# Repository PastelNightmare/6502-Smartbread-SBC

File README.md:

# Archiving, for now! I don't recommend using V1 of the board as of now.
As I play around with the finished PCB, I realized there are a few issues with it. 
- A13 is not connected to the RAM chip, so you have to make a jumper to it from elsewhere. 
- The below mentioned difference in clock generation from other processors to the WDC version.
- I'm using the WDC 65C22S, which does NOT have an open-drain interrupt output! It has a totem pole ouput! Right now, it's currently wired as if it were open drain, which is fine as long as you **don't use interrupts.** If you do though, you will short circuit the IRQ lines of the VIA.

# Upcoming hardware changes? 
- Reconnect A13, obviously.
- Make the system clock with WDC parts in mind
- Add schottky diodes on the VIA interrupts to connect them with the other open drain interrupts. Fine at 2mhz clock speed.
- Change address decoding to use Daryl Rictors DEC-1. https://sbc.rictor.org/decoder.html

# Upcoming software changes? 
- A customized version of EHBasic, which I've already made. Includes commands for sound, clearing screen, and returning to the monitor.
- Updating VGM player to load VGM out of RAM instead of ROM, and commented to explain better what it is doing. 
- Porting WozMon to this board for easier data entry. DeMon is fine, but it was more a project for me anyway. 
- A better terminal emulator program
- Eventually, using the new interrupts to allow streaming of VGM from the serial port. But that is a long time off. 

# IMPORTANT DESIGN NOTE
Due to a design difference with the WDC version of the 65C02 processor, this board will not work with WDC chips without a small modification. See "Using a WDC 65C02" below.

# SmartBread: A 6502 based single-board computer 
Its name came from a friend who called it this when they saw my initial prototypes on a breadboard. MintSpark Electronics was the working "maker name" for my projects, though it may not be for long. Other than another 6502 based single board computer, of which many exist, this was many firsts for me. Starting in 2017, I had a goal to build a 6502 system on a breadboard. As it grew, it became my first real endeavour into 6502 assembly, coding for an actual system, trying to make user friendly software, and PCB making. I now have working PCBs, a few programs, and much more work to do. 

Repo includes software, PCB gerber files and resources. ROM included has DeMon 4.0 and EhBASIC w/ its cold start monitor. Other files can be added and recompiled as desired 

Software assumes you are using the Kowalski 6502 simulator for assmebly. https://sbc.rictor.org/kowalski.html 

# Disclaimer: 
This was my first stab at assembly of any kind. While the code does exactly what I want it to do for this system, I understand that my code is not pretty by any stretch, and there is tons of room for improvement. I'm a novice, so please go easy on me. Some things like address decoding were figured out with the help of the 6502 forum and the 6502 Primer by Garth Wilson. Found at: http://wilsonminesco.com/

# Specs
- 65C02 processor running at 2mhz
- 2x 65C22 VIA (versatile interface adapter) chips
- 1x 65C51 ACIA (UART) chip
- SN76489 soundchip
- 32KB EEPROM (AT28C256)
- 16KB RAM (Alliance AS6C62256. 32kb chip, address decoding makes it 16kb)
- ATTINY26 for keyboard input
- Quad NAND gate 74 chip for address decoding
- Jumpers to fully configure serial port settings
- GPIO port, spare 8 bit parallel. 5v and GND also available. 
- PS2 keyboard input
- RCA output for sound. 
- Displays to charcter LCD or serial using any terminal device (board has a slot for the BatSocks tellymate tiny for this purpose http://www.batsocks.co.uk/products/Other/TellyMate%20Tiny.htm)

# Parts list
- R1-R6: 3.3k through hole resistor
- R7, R8: 10k through hole resistor
- R9: 370 ohm resistor. 
- C1: 1uf electrolytic capacitor. 
- All other capacitors: 100nf filter. Ceramic disc.
- 6502CLCK: ECS-100AX-018 oscillator, 2MHz
- SNCLCK: ECS-100AX-018 oscillator, 4MHz
- SERCLCK: ECS-100AX-018 oscillator, 1.8432MHz
- 65C02 processor
- VIA1, VIA2: 65C22 VIA chips (keyboard doesn't work right with non-CMOS versions)
- ACIA: 65C51 ACIA chip
- ROM: AT28C256
- RAM: Alliance AS6C62256
- ADDR: CD74HCT132E
- SN: Texas Instruments: SN76489
- ATTINY26: Atmel ATTINY26
- POWER: 5v through header, or surface mount USB Mini B jack. 

# Included Software
## DeMon 4.0
DeMon (DEvice MONitor) 4.0 is a basic memory monitor for the system. You can read the memory map, write to the memory map, run code, send commands directly to the sound chip, and much more. 
### Commands
All commands are processed by pressing enter. Accepts input from onboard PS2 keyboard or ACIA (with FTDI breakout)

| Command | Example | Description |         
| --------------- | --------------- | --------------- |
| Read  | 4000  | Displays data at address 0x4000  |
| List |L 2000.20FF| Will display all data between addresses 0x2000 and 0x20FF |
| Write  | W 2000 FF | Writes 0xFF at address 0x2000  |
| Write next | 00 | Data byte preceded with a space will write data to next location. MUST USE WRITE COMMAND FIRST |
| Run | R 2000 | Runs code starting at address 2000 | 
| Clear | CL | Clears all displays |
| Sound | S FF | Sends 0xFF to sound chip and makes the chip process it | 

## VGM player
A simple VGM player to play VGM files for the SN76489 sound chip. Expects raw VGM hex at 8900 (0900 if you're burning to ROM). Could easily be changed to load hex out of RAM instead with one line of code. 

## Enhanced 6502 BASIC 2.22 (EhBASIC) port
Made by Lee Davison, information: http://retro.hansotten.nl/6502-sbc/lee-davison-web-site/enhanced-6502-basic/. Ported to SmartBread by me. **COMPILING NOTE:** in order to compile EhBASIC, point the include line at the beginning of the Minimal Monitor to where you've downloaded EHBASIC.ASM. Minimal monitor starts at A000 and should be used to cold start BASIC! 

# Port Description
- GPIO - 8 bit parallel GPIO port. Can attach LCD to this port to work natively with DeMon, but it isn't required and can be used for whatever else the end user desires. The current board DOES NOT have the LCD enable line on this port, but it will be added to a future revision. 
- TM - Tellymate Tiny can be connected here for composite display. The part is discontinued, but eagle files and firmware exist on the Batsocks website. 
- Serial - Gives control lines for the ACIA ports, along with GNDs next to each one. Allows these status lines to be jumpered to ground, which **should** be done for most operations. (DTR, RTS, CTS, DCD) Also provides 5v and GND for user. Can connect to a TTL to RS232 converter for any type of serial display. 
- CLKMODE - Shorting these two pins with solder or a jumper allows the serial clock to also run the processor clock. This saves one part, but makes the CPU run slightly slower. 

# Using a WDC 65C02
In order to use a WDC version of the processor in the current revision, there is a slight modification to the board that must be made. Pin 39 (PHI2O) on the chip must be lifted out of the socket or removed. Then on the underside of the board, you must bridge a connection between Pin 39 and Pin 37 of the CPU socket. 

Traditionally, you provide the clock frequency to the CPU via PHI0/PHI2 input, then drive the rest of peripherals from PHI2O output from the CPU. The board was made with this in mind. WDC chips, however, do not test or guarantee the usability of the PHI2O output. They recommend that everything onboard receives its clock from the main oscillator driving the CPU. By bridging these two points on the board and lifting pin 39 from the chip, you are routing the clock in this manner. Future board revisions will have this as a jumper to ensure compatiblity. 

# To-do list / Wishlist 
- Update display to a new, non-discontinued solution. For now, Tellymate Tiny could be used, or provided serial pins can be attached to any device with a TTL to RS232 converter (Max232 and the like): Breakout USB boards, Converted RS232 port to a real glass terminal, etc. 
- Improve code by removing useless structures / subroutines
- Adding a binary load command to DeMon load binary data directly into memory from serial port. 
- Either standalone or built-in assembly evnironment for DeMon. 
- Text editor prorgram
- SPI protocol for various peripherals. 
- Cassette interface. 
- Rewrite my old code. The VGM player is old and hard to read. This was before I knew much about anything coding wise. 
- Write a terminal emulator program. I did make SimTerm originally, but it is hot garbage.

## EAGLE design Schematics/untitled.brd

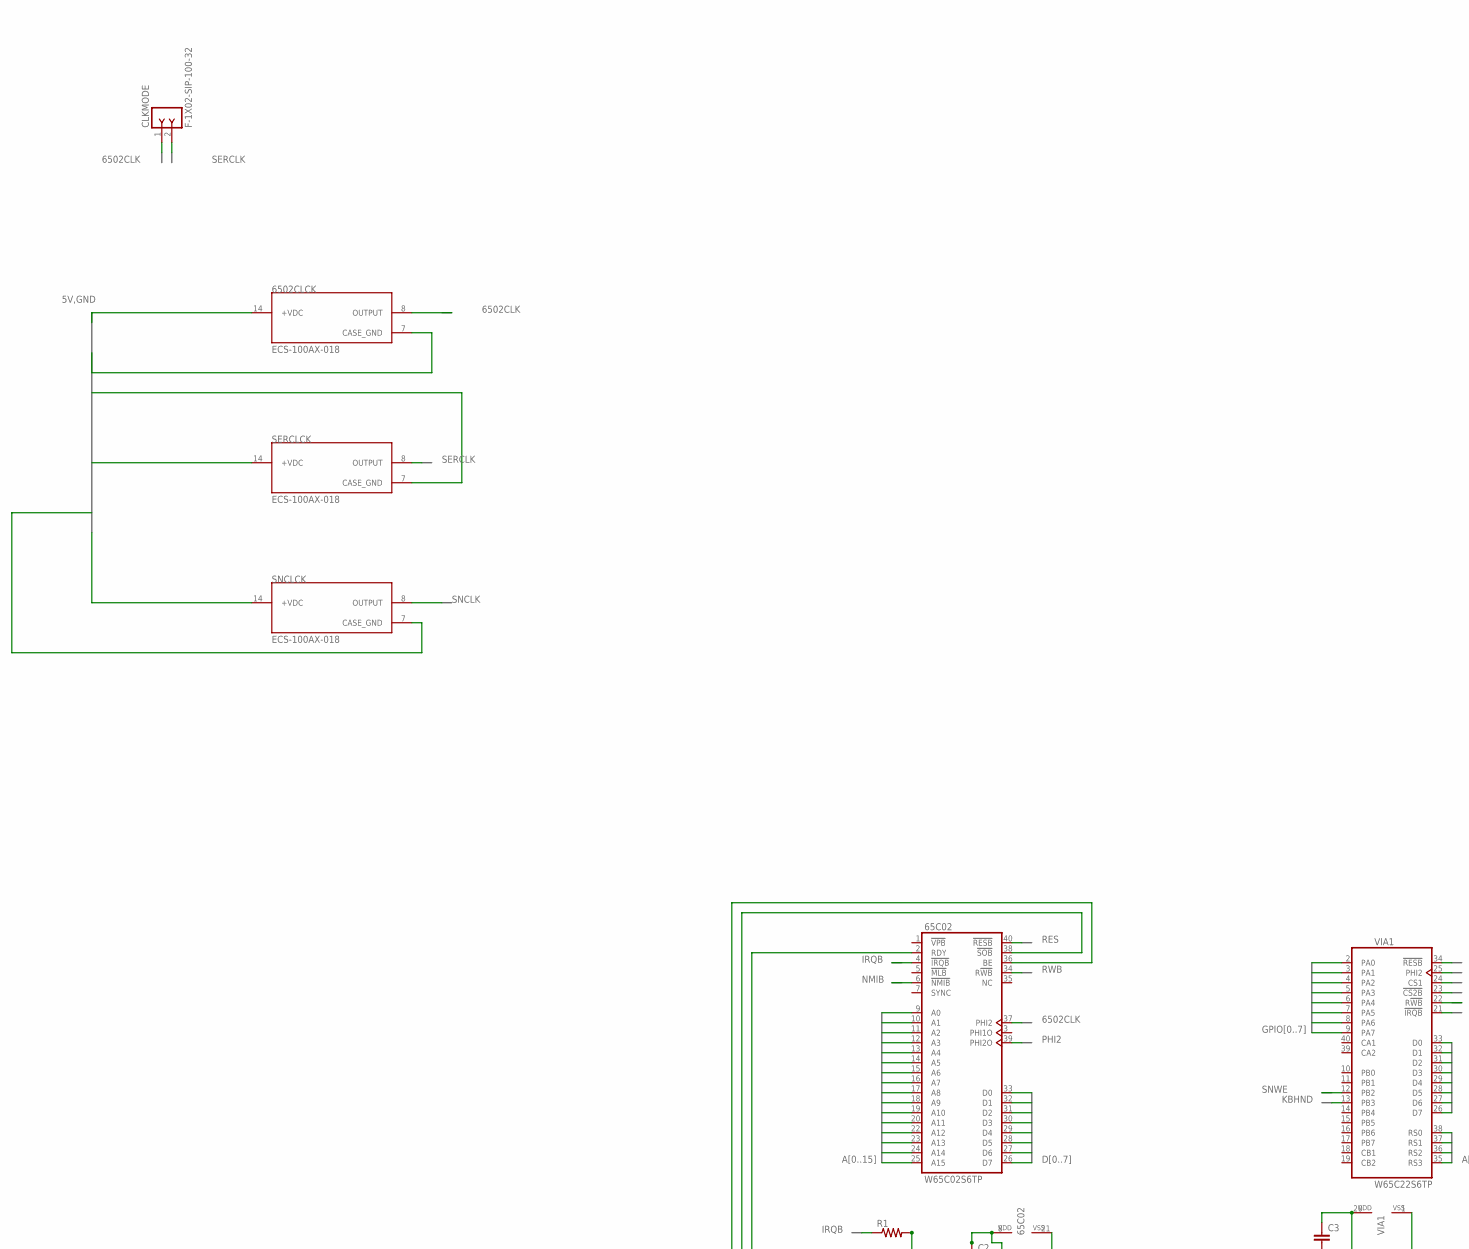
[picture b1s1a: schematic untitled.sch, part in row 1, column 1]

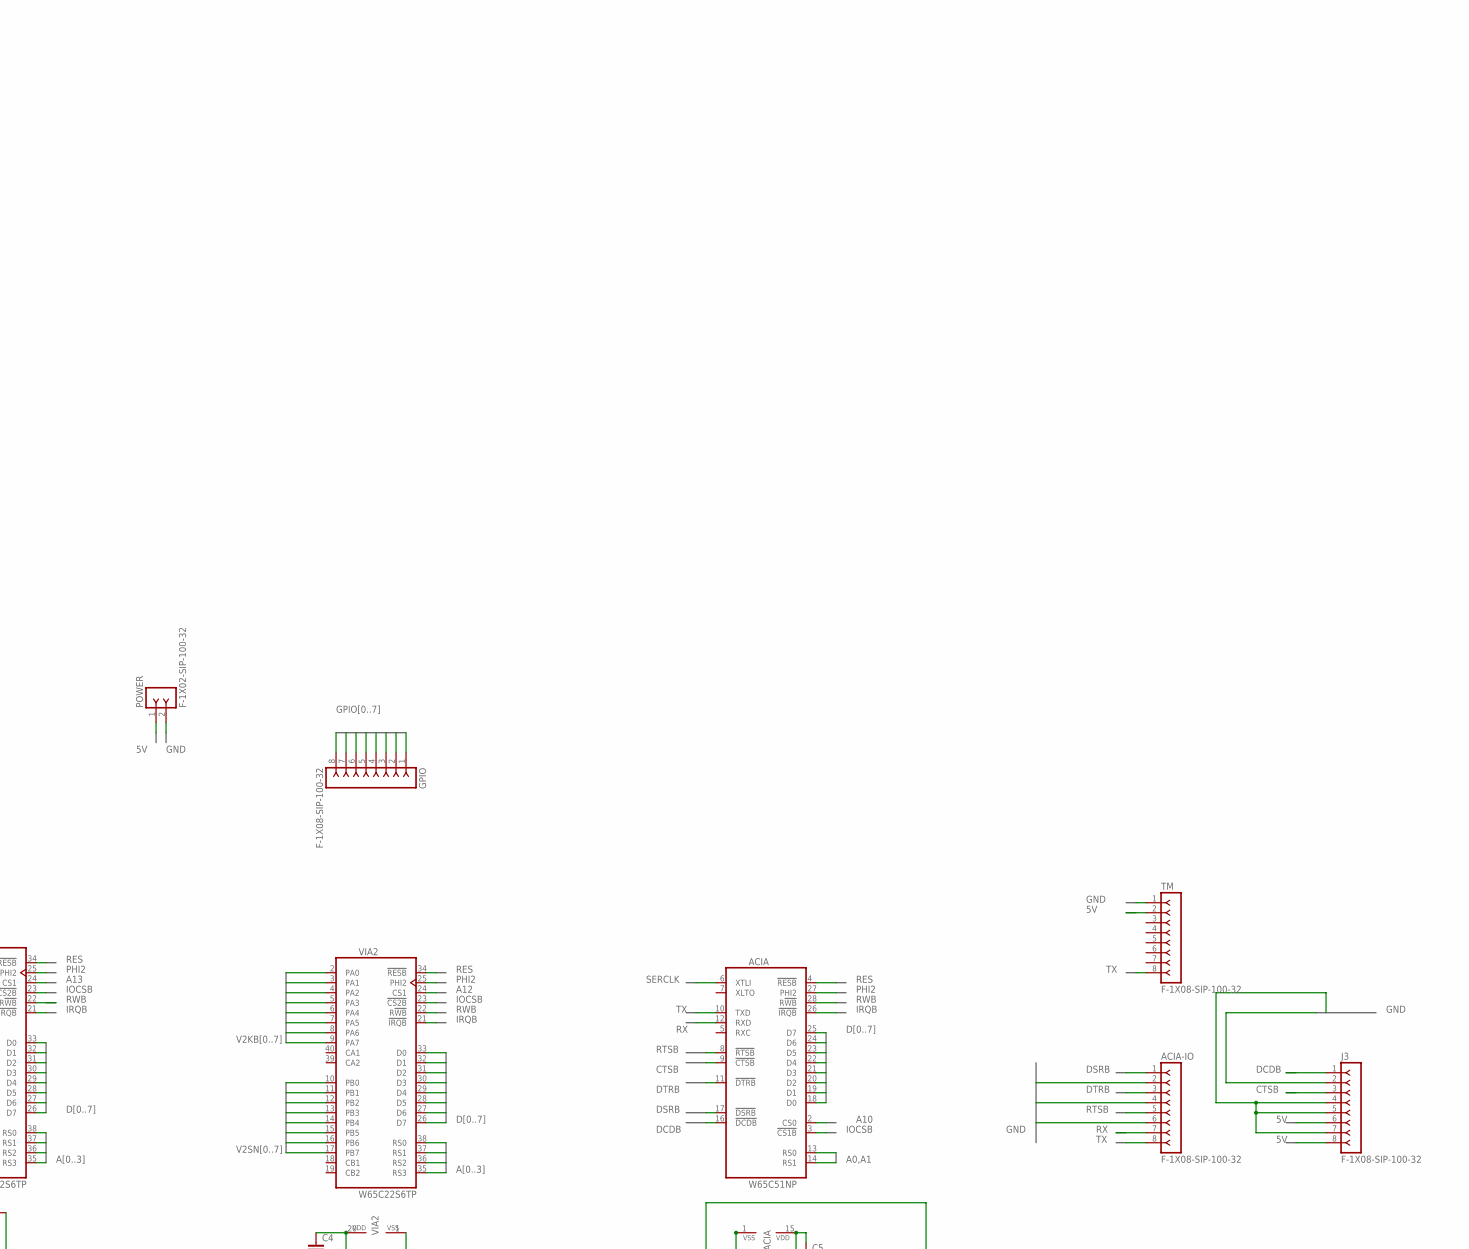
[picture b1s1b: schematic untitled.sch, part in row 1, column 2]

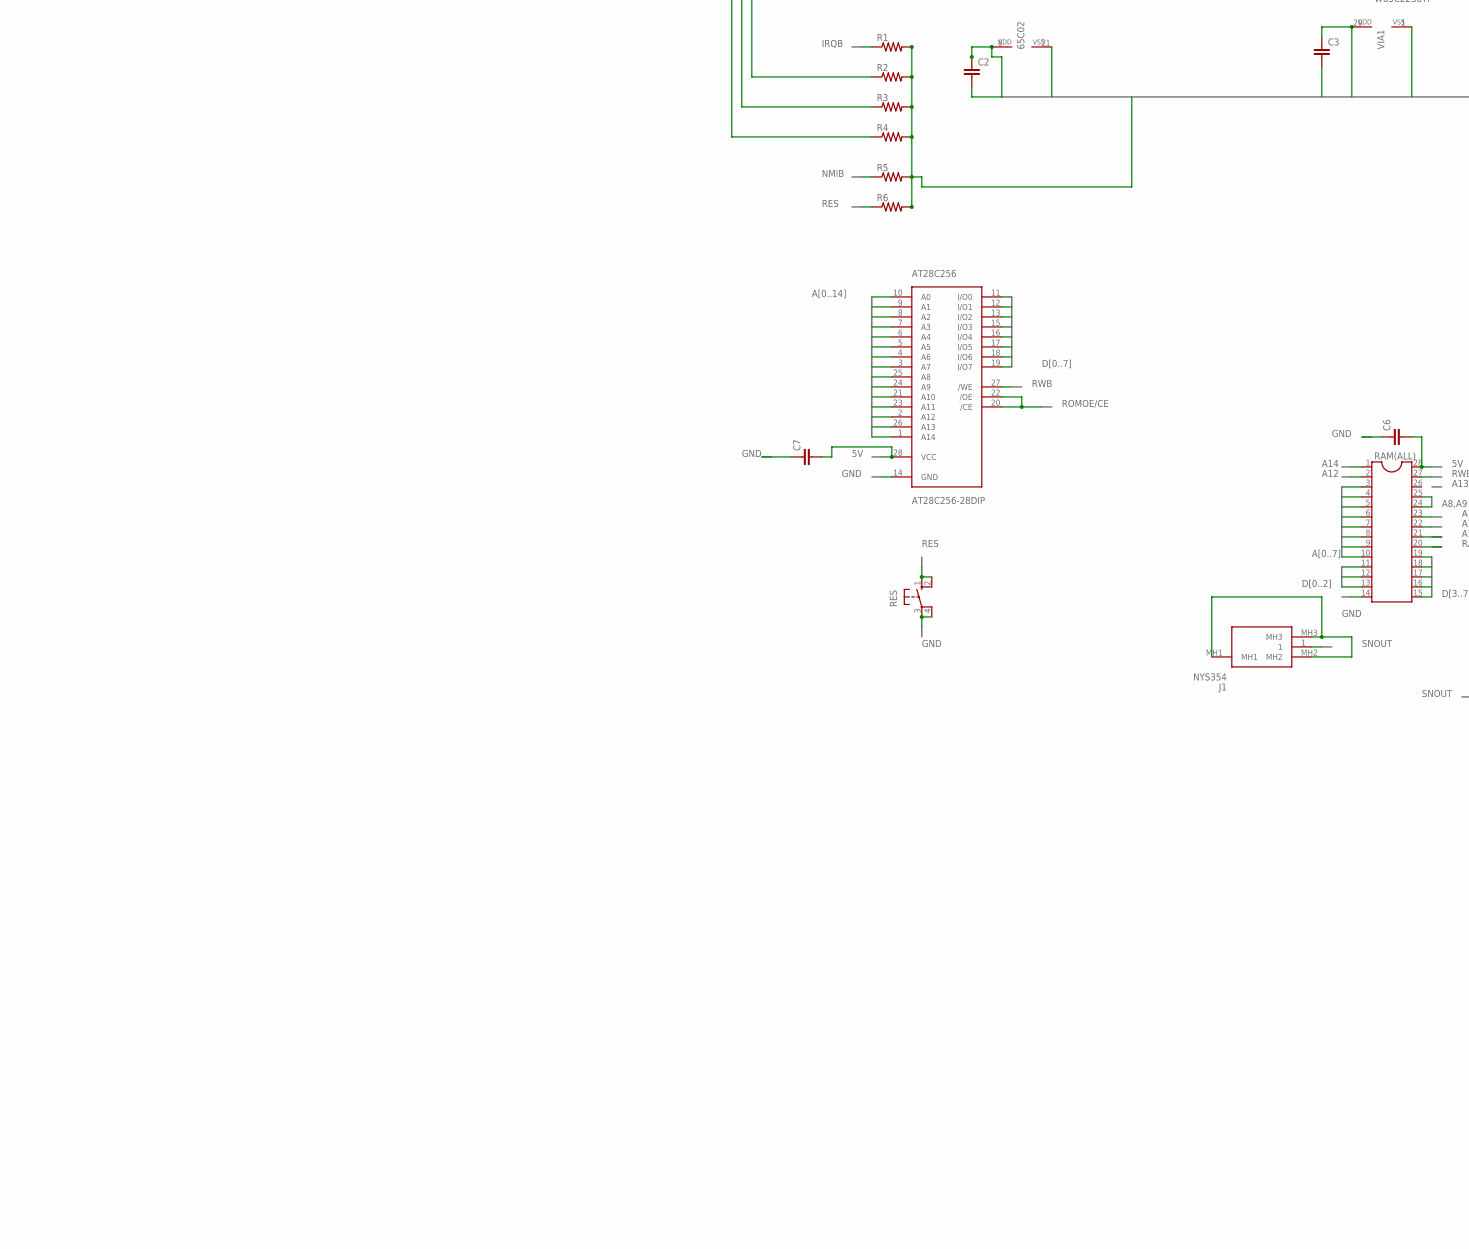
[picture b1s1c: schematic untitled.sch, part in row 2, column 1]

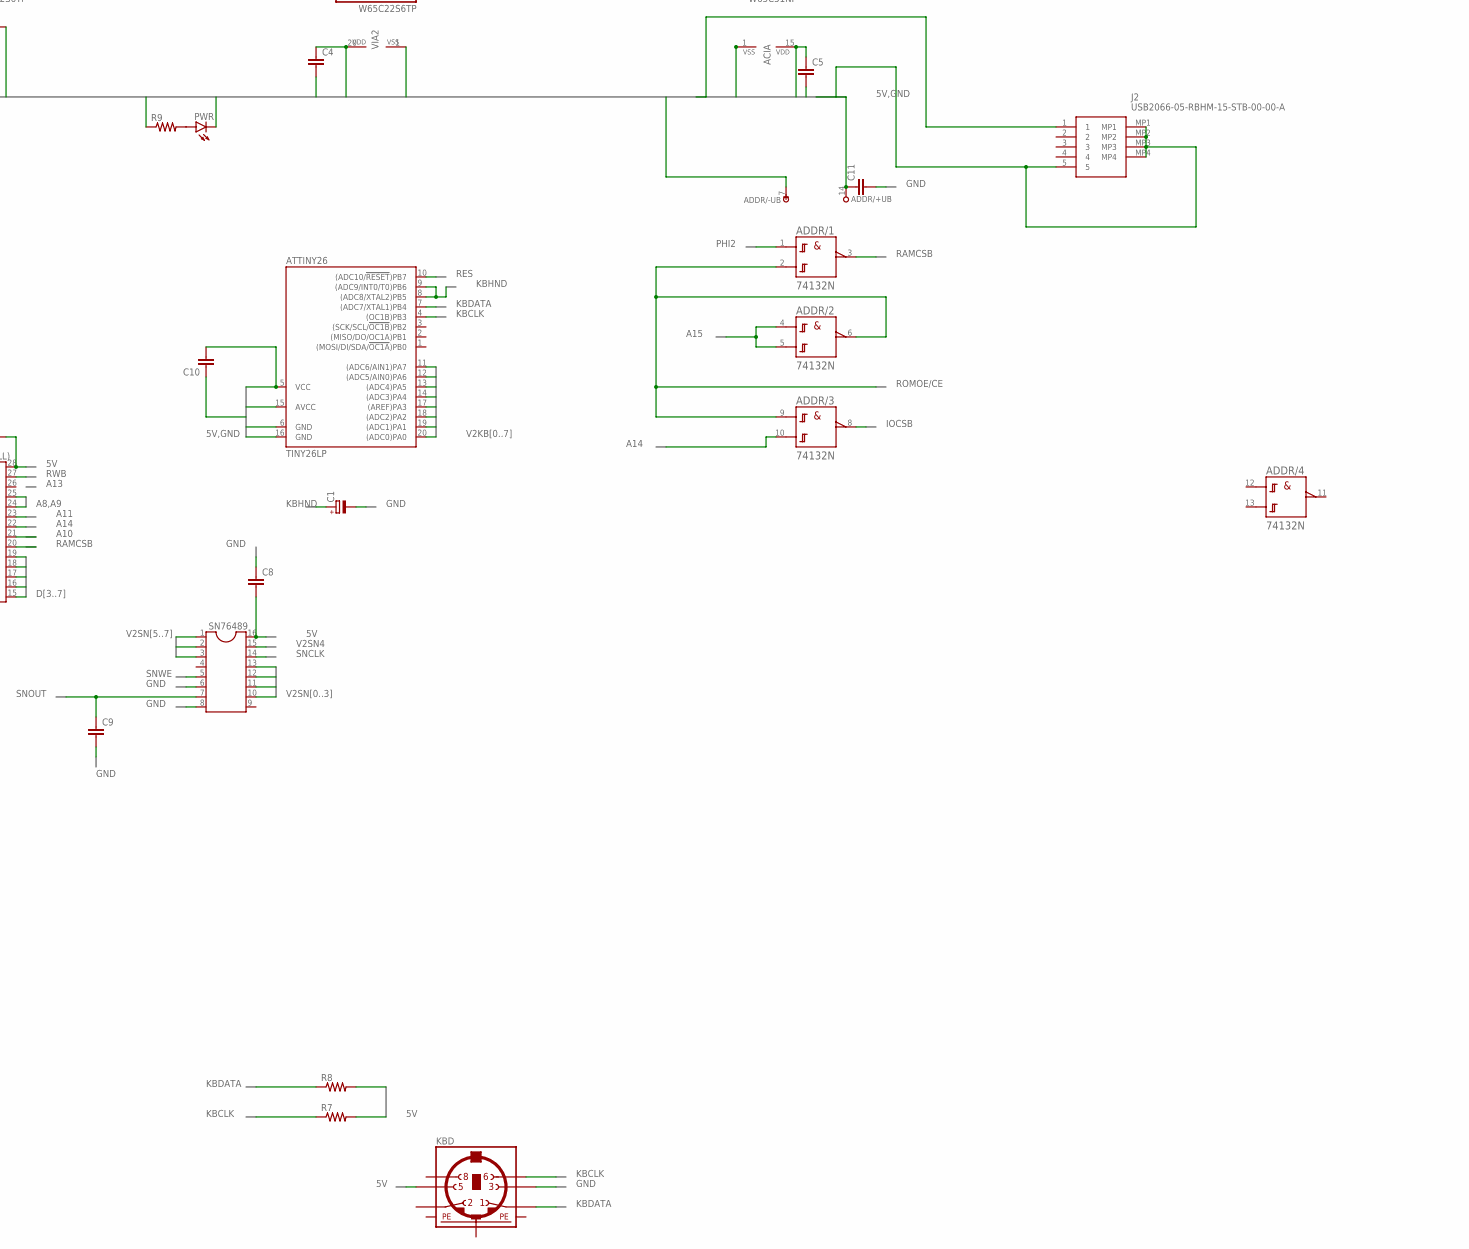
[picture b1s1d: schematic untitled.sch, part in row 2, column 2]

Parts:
65C02: W65C02S6TP; DIL40
6502CLCK: ECS-100AX-018; OSC_ECS-100AX-018
ACIA: W65C51NP; DIL28-6
ACIA-IO: F-1X08-SIP-100-32; SIP-100-08-32
ADDR: 74132N; DIL14
AT28C256: AT28C256-28DIP; DIL28-6
ATTINY26: TINY26LP; DIL20
C1: CPOL-EUE2,5-6E; E2,5-6E
C2, C3, C4, C5, C6, C7, C8, C9, C10, C11: C-EU025-024X044; C025-024X044
CLKMODE: F-1X02-SIP-100-32; SIP-100-02-32
GPIO: F-1X08-SIP-100-32; SIP-100-08-32
J1: NYS354
J2: USB2066-05-RBHM-15-STB-00-00-A; USB206605RBHM15STB0000A
J3: F-1X08-SIP-100-32; SIP-100-08-32
KBD: MINI_DIN_6; M_DIN6
POWER: F-1X02-SIP-100-32; SIP-100-02-32
PWR: LED5MM
R1, R2, R3, R4, R5, R6, R7, R8, R9: R-US_0204/7; 0204/7
RAM(ALL): DIL28; DIL28-6
RES: 10-XX; B3F-10XX
SERCLCK: ECS-100AX-018; OSC_ECS-100AX-018
SN76489: DIL16
SNCLCK: ECS-100AX-018; OSC_ECS-100AX-018
TM: F-1X08-SIP-100-32; SIP-100-08-32
VIA1, VIA2: W65C22S6TP; DIL40

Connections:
5V: 65C02.8 (VDD), 6502CLCK.14 (+VDC), ACIA.15 (VDD), ADDR.14 (+UB), AT28C256.28 (VCC), ATTINY26.5 (VCC), ATTINY26.15 (AVCC), C2.1, C3.1, C4.1, C5.1, C6.2, C7.2, C8.2, C10.2, C11.1, J2.1, J3.6, J3.8, KBD.5, POWER.1, R1.2, R2.2, R3.2, R4.2, R5.2, R6.2, R7.2, R8.2, R9.1, RAM(ALL).28, SERCLCK.14 (+VDC), SN76489.16, SNCLCK.14 (+VDC), TM.2, VIA1.20 (VDD), VIA2.20 (VDD)
6502CLK: 65C02.37 (PHI2), 6502CLCK.8 (OUTPUT), CLKMODE.1
A0: 65C02.9 (A0), ACIA.13 (RS0), AT28C256.10 (A0), RAM(ALL).10, VIA1.38 (RS0), VIA2.38 (RS0)
A1: 65C02.10 (A1), ACIA.14 (RS1), AT28C256.9 (A1), RAM(ALL).9, VIA1.37 (RS1), VIA2.37 (RS1)
A2: 65C02.11 (A2), AT28C256.8 (A2), RAM(ALL).8, VIA1.36 (RS2), VIA2.36 (RS2)
A3: 65C02.12 (A3), AT28C256.7 (A3), RAM(ALL).7, VIA1.35 (RS3), VIA2.35 (RS3)
A4: 65C02.13 (A4), AT28C256.6 (A4), RAM(ALL).6
A5: 65C02.14 (A5), AT28C256.5 (A5), RAM(ALL).5
A6: 65C02.15 (A6), AT28C256.4 (A6), RAM(ALL).4
A7: 65C02.16 (A7), AT28C256.3 (A7), RAM(ALL).3
A8: 65C02.17 (A8), AT28C256.25 (A8), RAM(ALL).25
A9: 65C02.18 (A9), AT28C256.24 (A9), RAM(ALL).24
A10: 65C02.19 (A10), ACIA.2 (CS0), AT28C256.21 (A10), RAM(ALL).21
A11: 65C02.20 (A11), AT28C256.23 (A11), RAM(ALL).23
A12: 65C02.22 (A12), AT28C256.2 (A12), RAM(ALL).2, VIA2.24 (CS1)
A13: 65C02.23 (A13), AT28C256.26 (A13), VIA1.24 (CS1)
A14: 65C02.24 (A14), ADDR.10 (B), AT28C256.1 (A14), RAM(ALL).1, RAM(ALL).22
A15: 65C02.25 (A15), ADDR.4 (A), ADDR.5 (B)
CTSB: ACIA.9 (!CTSB), J3.3
D0: 65C02.33 (D0), ACIA.18 (D0), AT28C256.11 (I/O0), RAM(ALL).11, VIA1.33 (D0), VIA2.33 (D0)
D1: 65C02.32 (D1), ACIA.19 (D1), AT28C256.12 (I/O1), RAM(ALL).12, VIA1.32 (D1), VIA2.32 (D1)
D2: 65C02.31 (D2), ACIA.20 (D2), AT28C256.13 (I/O2), RAM(ALL).13, VIA1.31 (D2), VIA2.31 (D2)
D3: 65C02.30 (D3), ACIA.21 (D3), AT28C256.15 (I/O3), RAM(ALL).15, VIA1.30 (D3), VIA2.30 (D3)
D4: 65C02.29 (D4), ACIA.22 (D4), AT28C256.16 (I/O4), RAM(ALL).16, VIA1.29 (D4), VIA2.29 (D4)
D5: 65C02.28 (D5), ACIA.23 (D5), AT28C256.17 (I/O5), RAM(ALL).17, VIA1.28 (D5), VIA2.28 (D5)
D6: 65C02.27 (D6), ACIA.24 (D6), AT28C256.18 (I/O6), RAM(ALL).18, VIA1.27 (D6), VIA2.27 (D6)
D7: 65C02.26 (D7), ACIA.25 (D7), AT28C256.19 (I/O7), RAM(ALL).19, VIA1.26 (D7), VIA2.26 (D7)
DCDB: ACIA.16 (!DCDB), J3.1
DSRB: ACIA.17 (!DSRB), ACIA-IO.1
DTRB: ACIA.11 (!DTRB), ACIA-IO.3
GND: 65C02.21 (VSS), 6502CLCK.7 (CASE_GND), ACIA.1 (VSS), ACIA-IO.2, ACIA-IO.4, ACIA-IO.6, ADDR.7 (-UB), AT28C256.14 (GND), ATTINY26.6 (GND), ATTINY26.16 (GND), C1.-, C2.2, C3.2, C4.2, C5.2, C6.1, C7.1, C8.1, C9.2, C10.1, C11.2, J2.5, J2.MP1, J2.MP2, J2.MP3, J2.MP4, J3.2, J3.4, J3.5, J3.7, KBD.3, POWER.2, PWR.K (C), RAM(ALL).14, RES.3, RES.4 (P1), SERCLCK.7 (CASE_GND), SN76489.6, SN76489.8, SNCLCK.7 (CASE_GND), TM.1, VIA1.1 (VSS), VIA2.1 (VSS)
GPIO0: GPIO.1, VIA1.2 (PA0)
GPIO1: GPIO.2, VIA1.3 (PA1)
GPIO2: GPIO.3, VIA1.4 (PA2)
GPIO3: GPIO.4, VIA1.5 (PA3)
GPIO4: GPIO.5, VIA1.6 (PA4)
GPIO5: GPIO.6, VIA1.7 (PA5)
GPIO6: GPIO.7, VIA1.8 (PA6)
GPIO7: GPIO.8, VIA1.9 (PA7)
IOCSB: ACIA.3 (!CS1B), ADDR.8 (Y), VIA1.23 (!CS2B), VIA2.23 (!CS2B)
IRQB: 65C02.4 (!IRQB), ACIA.26 (!IRQB), R1.1, VIA1.21 (!IRQB), VIA2.21 (!IRQB)
KBCLK: ATTINY26.4 ((OC1B)PB3), KBD.6, R7.1
KBDATA: ATTINY26.7 ((ADC7/XTAL1)PB4), KBD.1, R8.1
KBHND: ATTINY26.8 ((ADC8/XTAL2)PB5), ATTINY26.9 ((ADC9/INT0/T0)PB6), C1.+, VIA1.13 (PB3)
unnamed: 65C02.36 (BE), R4.1
unnamed: PWR.A, R9.2
unnamed: 65C02.2 (RDY), R2.1
unnamed: 65C02.38 (!SOB), R3.1
unnamed: J1.MH1, J1.MH2, J1.MH3
NMIB: 65C02.6 (!NMIB), R5.1
PE1: KBD.SH1 (PE1)
PE2: KBD.SH2 (PE2)
PE3: KBD.SH3 (PE3)
PHI2: 65C02.39 (PHI2O), ACIA.27 (PHI2), ADDR.1 (A), VIA1.25 (PHI2), VIA2.25 (PHI2)
RAMCSB: ADDR.3 (Y), RAM(ALL).20
RES: 65C02.40 (!RESB), ACIA.4 (!RESB), ATTINY26.10 ((ADC10/!RESET!)PB7), R6.1, RES.1 (S), RES.2 (S1), VIA1.34 (!RESB), VIA2.34 (!RESB)
ROMOE/CE: ADDR.2 (B), ADDR.6 (Y), ADDR.9 (A), AT28C256.20 (/CE), AT28C256.22 (/OE)
RTSB: ACIA.8 (!RTSB), ACIA-IO.5
RWB: 65C02.34 (R!WB), ACIA.28 (R!WB), AT28C256.27 (/WE), RAM(ALL).27, VIA1.22 (R!WB), VIA2.22 (R!WB)
RX: ACIA.12 (RXD), ACIA-IO.7
SERCLK: ACIA.6 (XTLI), CLKMODE.2, SERCLCK.8 (OUTPUT)
SNCLK: SN76489.14, SNCLCK.8 (OUTPUT)
SNOUT: C9.1, J1.1, SN76489.7
SNWE: SN76489.5, VIA1.12 (PB2)
TX: ACIA.10 (TXD), ACIA-IO.8, TM.8
V2KB0: ATTINY26.20 ((ADC0)PA0), VIA2.2 (PA0)
V2KB1: ATTINY26.19 ((ADC1)PA1), VIA2.3 (PA1)
V2KB2: ATTINY26.18 ((ADC2)PA2), VIA2.4 (PA2)
V2KB3: ATTINY26.17 ((AREF)PA3), VIA2.5 (PA3)
V2KB4: ATTINY26.14 ((ADC3)PA4), VIA2.6 (PA4)
V2KB5: ATTINY26.13 ((ADC4)PA5), VIA2.7 (PA5)
V2KB6: ATTINY26.12 ((ADC5/AIN0)PA6), VIA2.8 (PA6)
V2KB7: ATTINY26.11 ((ADC6/AIN1)PA7), VIA2.9 (PA7)
V2SN0: SN76489.10, VIA2.10 (PB0)
V2SN1: SN76489.11, VIA2.11 (PB1)
V2SN2: SN76489.12, VIA2.12 (PB2)
V2SN3: SN76489.13, VIA2.13 (PB3)
V2SN4: SN76489.15, VIA2.14 (PB4)
V2SN5: SN76489.1, VIA2.15 (PB5)
V2SN6: SN76489.2, VIA2.16 (PB6)
V2SN7: SN76489.3, VIA2.17 (PB7)

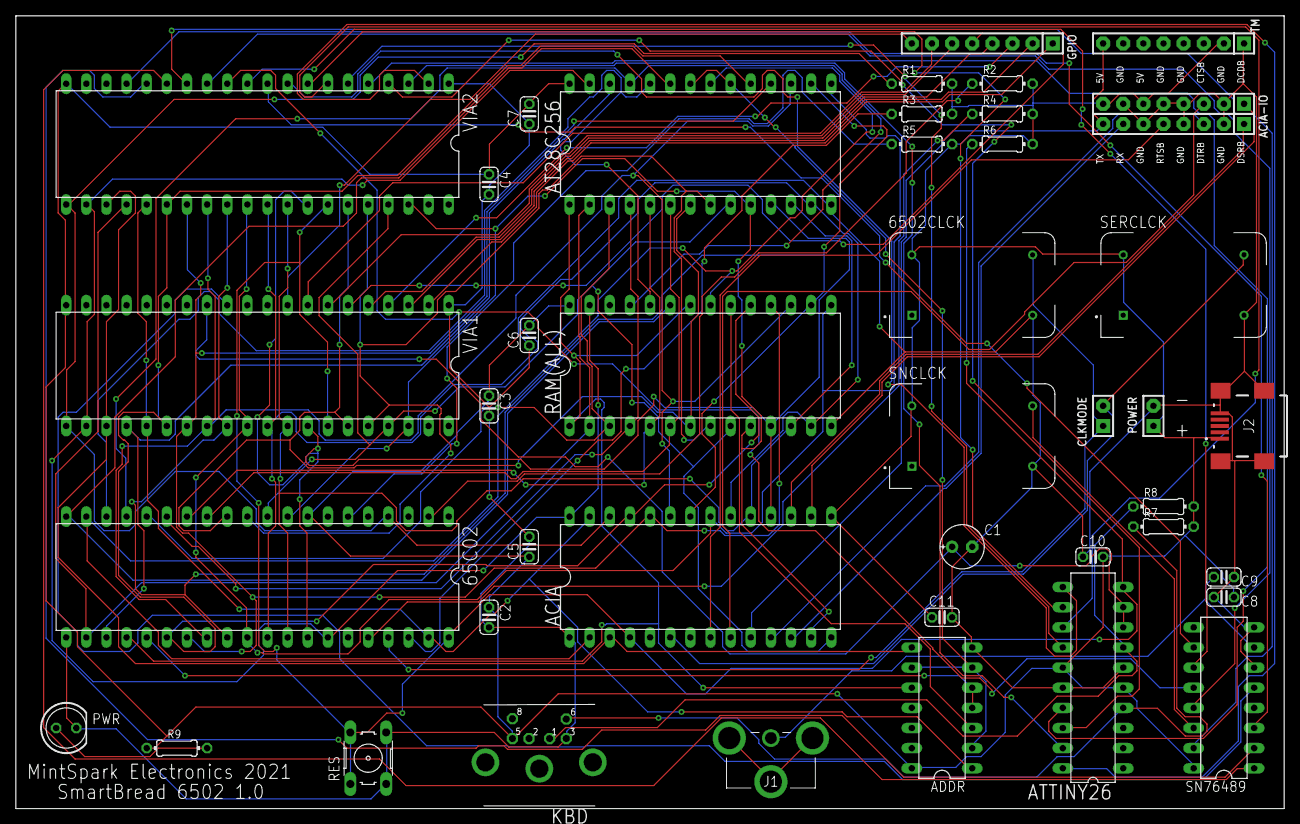
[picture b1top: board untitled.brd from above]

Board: 2 copper layers, 160.0 x 100.0 mm, 43 parts (0 on the bottom side), 78 nets.

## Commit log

2023-06-09 Add files via upload
    Premade ROM binary for SmartBread. Includes EHBASIC, its cold-start monitor, and DeMon 4.0
2025-10-24 Update README with WDC 65C02 usage instructions
    Added important design note regarding WDC 65C02 compatibility and modification instructions.
2025-10-24 Update README.md
    Spelling errors
2025-10-27 Space Saving Conditional Blocks
    Start of the first refactoring I'm doing. Allows user to set at run time if they'll be using a character LCD and Tellymate Tiny or not. If not, they won't be assembled. Saves space and enables GPIO p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
2025-11-08 Update README with archiving notes and future plans
    Added notes on hardware and software changes for the board.

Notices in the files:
parts and their libraries:
con-headers-jp: Copyright (C) 2008, Bob Starr
